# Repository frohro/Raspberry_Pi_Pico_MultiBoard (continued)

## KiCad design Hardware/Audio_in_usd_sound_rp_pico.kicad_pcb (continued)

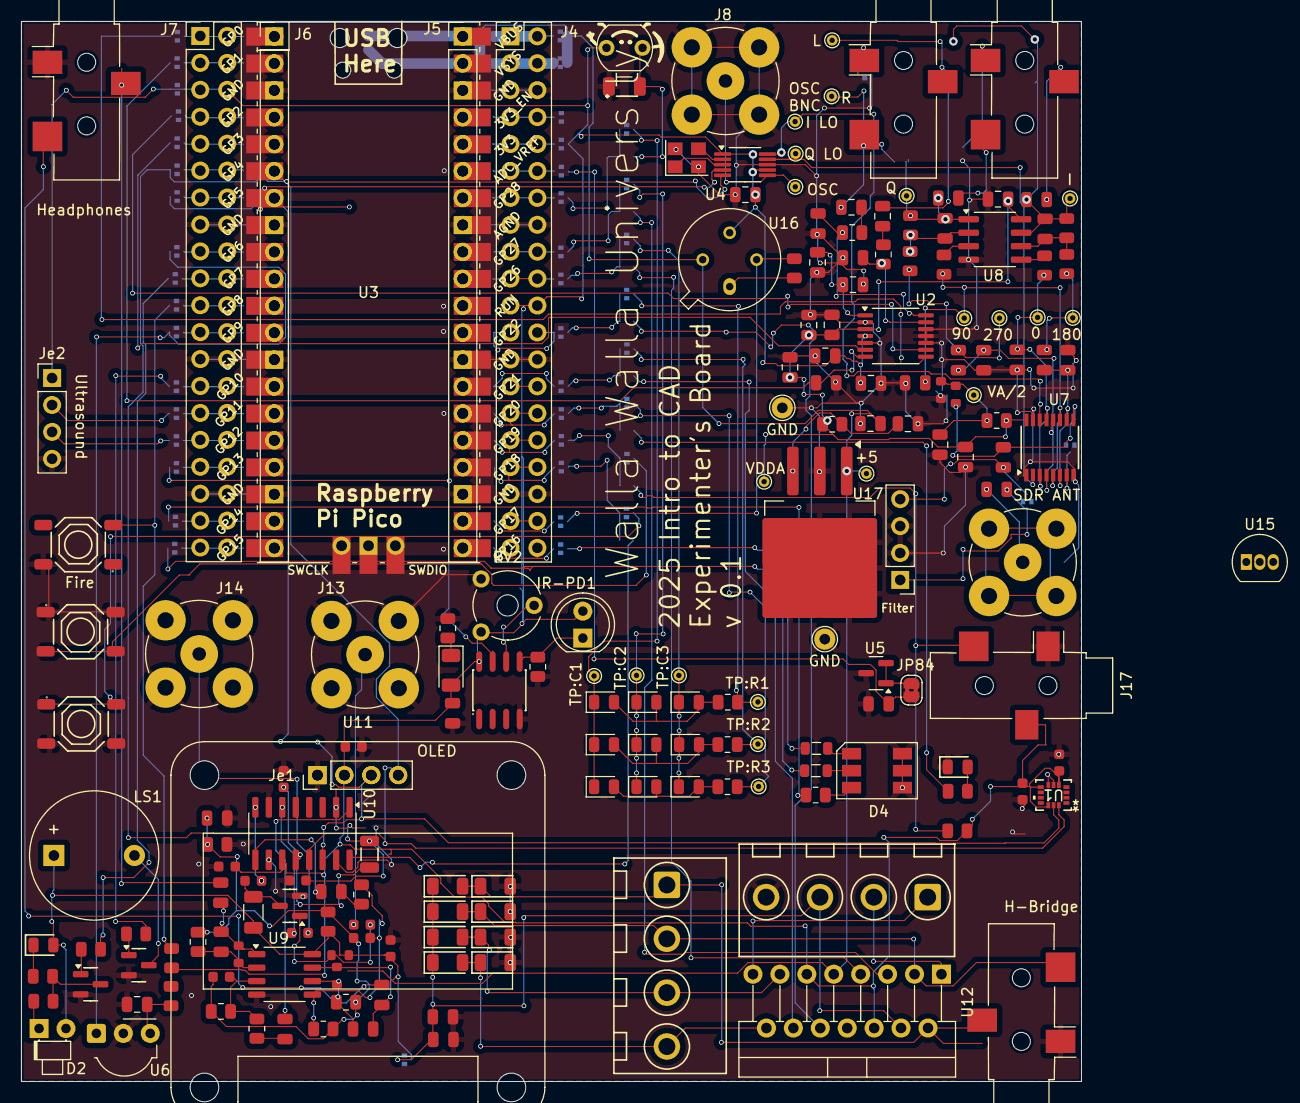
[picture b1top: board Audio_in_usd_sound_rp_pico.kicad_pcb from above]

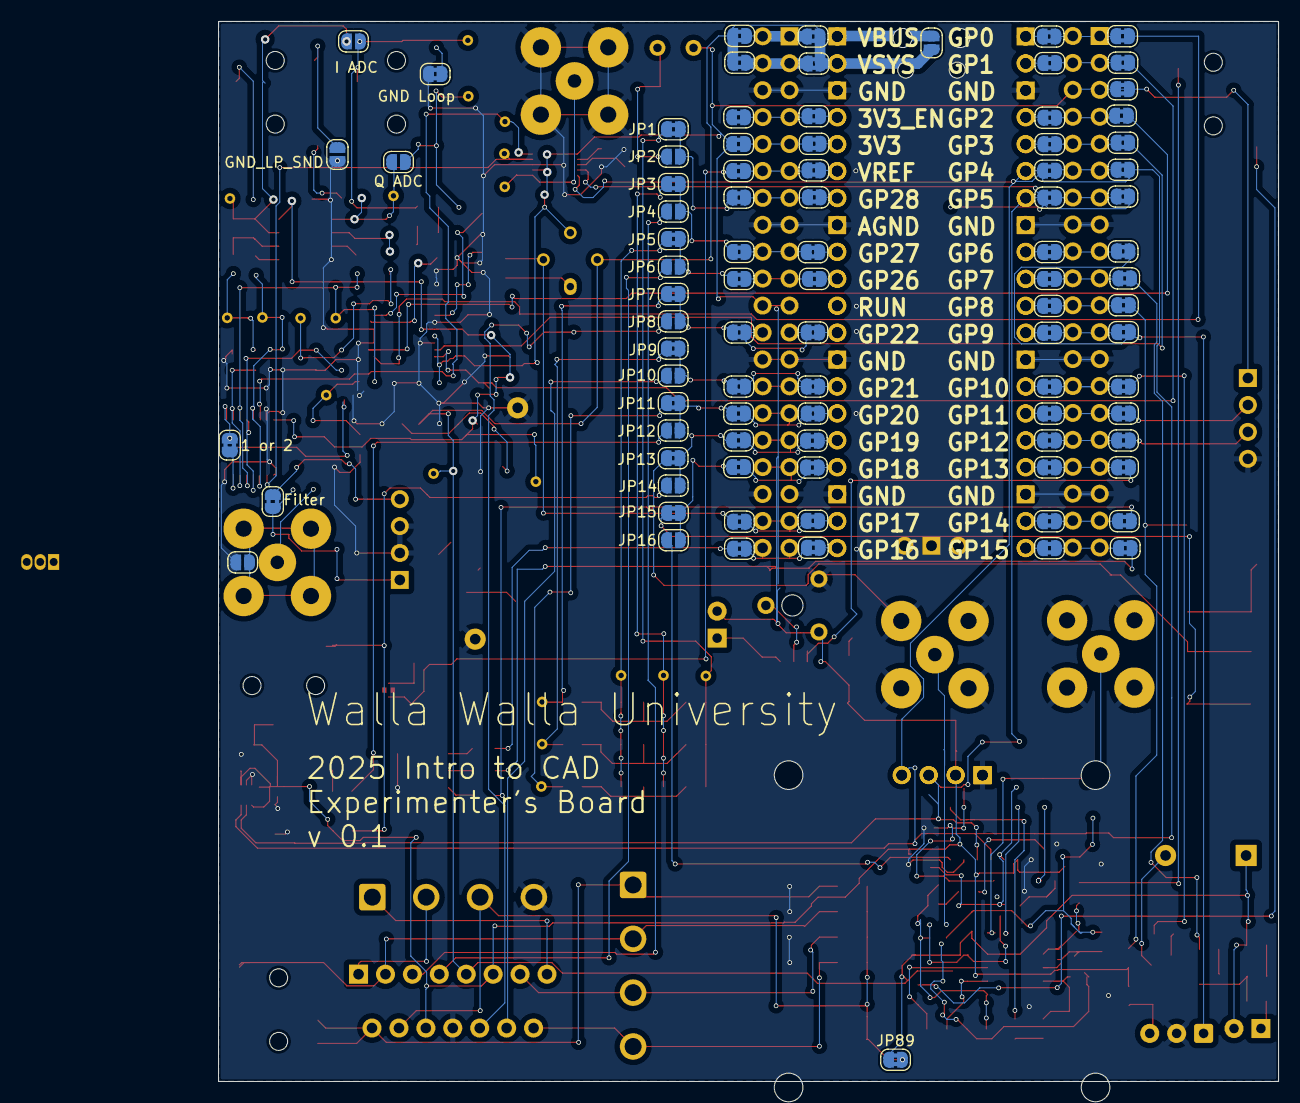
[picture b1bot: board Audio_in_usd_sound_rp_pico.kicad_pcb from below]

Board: 2 copper layers, 100.0 x 100.0 mm, 275 parts (88 on the bottom side), 189 nets.

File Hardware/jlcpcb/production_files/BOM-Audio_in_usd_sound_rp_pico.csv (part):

Comment,Designator,Footprint,LCSC,Quantity
PhotoResistor,R37,R_LDR_5.1x4.3mm_P3.4mm_Vertical,C10077,1
220pF,"C14,C33,C42",C_0805,C107145,3
TSOP4438,U6,Vishay_MOLD-3Pin,C124647,1
100nF,"C2,C38,C41,C47,C48,C52",C_0603,C14663,6
MS5351M,U4,MSOP-10_3x3mm_P0.5mm,C1509083,1
10uF,"C12,C31,C32,C39,C40,C44,C45,C56,C57,C8,C9",C_0805_2012Metric,C15850,11
2.2nF,"C35,C54",C_0603,C1604,2
22pF,"C36,C37",C_0603,C1653,2
100Ω,"R31,R4,R43",R_0805,C17408,3
10k,"R12,R42,R6",R_0805_2012Metric,C17414,3
10Ω,"R13,R14,R15,R16",R_0805,C17415,4
4.7nF,"C16,C21,C22,C24,C27,C6,C7",C_0805,C1744,7
15k,R25,R_0805_2012Metric,C17475,1
1kΩ,"R7,R8",R_0805,C17513,2
200,"R2,R3",R_0805_2012Metric,C17544,2
2kΩ,"R17,R18,R29,R30",R_0805,C17604,4
3.9k,"R23,R28",R_0805_2012Metric,C17614,2
33Ω,R9,R_0805,C17634,1
680,"R39,R40,R41",R_0805_2012Metric,C17798,3
68Ω,R5,R_0805,C17802,1
8.2k,"R21,R27",R_0805_2012Metric,C17828,2
100pF,"C28,C29",C_0805,C1790,2
1kΩ,R38,R_1206_3216Metric,C17902,1
1N4004W,"D10,D11,D12,D5,D6,D7,D8,D9",D_SOD-123FL,C18199087,8
IR LED IR908-7C-F,D2,LED_D1.8mm_W1.8mm_H2.4mm_Horizontal_O1.27mm_Z8.2mm,C183794,1
ADC IN,"J1,J12,J15,J16,J17",Jack_3.5mm_CUI_SJ-3523-SMT_Horizontal,C18594,5
L298N,U12,TO-220-15_P2.54x2.54mm_StaggerOdd_Lead4.58mm_Vertical,C19922,1
1kΩ,R11,R_0603,C21190,1
Si4732,U10,SOIC-16_3.9x9.9mm_P1.27mm,C2155558,1
DS18B20A10T6,U15,TO-92_Inline,C22360667,1
Green,"D1,D3",D_0805,C2297,2
39kΩ,"R10,R20",R_0603,C23153,2
1,R44,R_0805_2012Metric,C25271,1
B 100Ω,"R32,R33",L_0805_2012Metric,C25277,2
100kΩ,R22,R_0603,C25803,1
10kΩ,R1,R_0603,C25804,1
Conn_01x04_Socket,"Je1,Je2,Je3",PinHeader_1x04_P2.54mm_Vertical_Female,C2718488,3
1uF,"C18,C19,C25,C26,C3,C4,C46",C_0805,C28323,7
LM2937xS,U17,TO-263-3_TabPin2,C2902486,1
Conn_01x20,"J5,J6",PinHeader_1x20_P2.54mm_Vertical,C2905423,2
Conn_02x20_Counter_Clockwise,"J4,J7",PinSocket_2x20_P2.54mm_Vertical_Counterclockwise,C2977589,2
"Screw Terminal, 4Px5.08mm, 20A","T1,T2",CONN-TH_4P-P5.08_DB129VG-5.08-4P-GN-S,C2981774,2
PI5C3253CQEX,U7,SSOP-16_3.9x4.9mm_P0.635mm,C3001703,1
CJ431,U5,SOT-23,C3113,1
"Tactile Button, 160gf","S2,SW1,SW2",SW-SMD_4P-L5.1-W5.1-P3.70-LS6.5-TL-2,C318884,3
Q13FC1350000400,X1,FC-135R_L3.2-W1.5,C32346,1
Speaker,LS1,Buzzer_12x9.5RM7.6,C409842,1
1k,R24,R_1206_3216Metric,C4410,1
0.1uF,"C10,C11,C13,C15,C20,C23,C30,C49,C50,C51,C55",C_0805_2012Metric,C49678,11
~,U16,TO-33-4_Window-Taylan,C5380082,1
PCM1808PWR,U2,TSSOP-14_4.4x5mm_P0.65mm,C55513,1
10nF,"C34,C43",C_0603,C57112,2
MMBT2222A,Q3,Q_SOT-23,C7420351,1
LM393DR2G,U13,SOIC-8_L5.0-W4.0-P1.27-LS6.0-BL,C7955,1
LED,"D13,D14,D15,D16,D17,D18,D19,D20,D21",LED_0805_2012Metric,C84256,9
MMBT2222A 1P,"Q1,Q2",Q_SOT-23,C8512,2
X322525MSB4SI,Y1,Crystal_SMD_3225-4Pin_3.2x2.5mm,C9006,1
OPA1612AxD,U8,SOIC-8_3.9x4.9mm_P1.27mm,C94590,1
LSM6DSO32TR,U1,LGA-14L_2P5X3X0P83_STM,,1
LM358,U9,SOP-8_3.9x4.9mm_P1.27mm,,1
ANT_BNC,J14,BNC_TEConnectivity_1478204_Vertical,,1
I LO,TP3,TestPoint_THTPad_D1.0mm_Drill0.5mm,,1
Q LO,TP4,TestPoint_THTPad_D1.0mm_Drill0.5mm,,1
10K,R35,R_0805_2012Metric,,1
+5,TP25,TestPoint_THTPad_D1.0mm_Drill0.5mm,,1
VA/2,TP11,TestPoint_THTPad_D1.0mm_Drill0.5mm,,1
15k,R19,R_0805_2012Metric,,1
90,TP16,TestPoint_THTPad_D1.0mm_Drill0.5mm,,1
0.1uF,C17,C_0805_2012Metric,,1
R 300Ω,R34,R_0805_2012Metric,,1
0,TP14,TestPoint_THTPad_D1.0mm_Drill0.5mm,,1
GND,TP10,TestPoint_THTPad_D2.0mm_Drill1.0mm,,1
OSC,TP5,TestPoint_THTPad_D1.0mm_Drill0.5mm,,1
GND,TP12,TestPoint_THTPad_D2.0mm_Drill1.0mm,,1
L,TP1,TestPoint_THTPad_D1.0mm_Drill0.5mm,,1
Jumper_2_Bridged,JP84,SolderJumper-2_P1.3mm_Bridged2Bar_RoundedPad1.0x1.5mm,,1
270,TP15,TestPoint_THTPad_D1.0mm_Drill0.5mm,,1
BNC,J8,BNC_TEConnectivity_1478204_Vertical,,1
270R,R36,R_0805_2012Metric,,1
SDR ANT,J11,BNC_TEConnectivity_1478204_Vertical,,1
Q,TP18,TestPoint_THTPad_D1.0mm_Drill0.5mm,,1
180,TP13,TestPoint_THTPad_D1.0mm_Drill0.5mm,,1
C784540,D4,LED footprint,,1
VDDA,TP26,TestPoint_THTPad_D1.0mm_Drill0.5mm,,1
R,TP2,TestPoint_THTPad_D1.0mm_Drill0.5mm,,1
R_Potentiometer_US,RV2,Potentiometer_Piher_PT-6-V_Vertical_Hole,,1
I,TP17,TestPoint_THTPad_D1.0mm_Drill0.5mm,,1
ANT_BNC,J13,BNC_TEConnectivity_1478204_Vertical,,1
Jumper_2_Open,JP12,SolderJumper-2_P1.3mm_Open_RoundedPad1.0x1.5mm,,1
Jumper_2_Bridged,JP28,SolderJumper-2_P1.3mm_Bridged2Bar_RoundedPad1.0x1.5mm,,1
Jumper_2_Bridged,JP41,SolderJumper-2_P1.3mm_Bridged2Bar_RoundedPad1.0x1.5mm,,1
Jumper_2_Bridged,JP66,SolderJumper-2_P1.3mm_Bridged2Bar_RoundedPad1.0x1.5mm,,1
Jumper_2_Bridged,JP83,SolderJumper-2_P1.3mm_Bridged2Bar_RoundedPad1.0x1.5mm,,1
Jumper_2_Open,JP8,SolderJumper-2_P1.3mm_Open_RoundedPad1.0x1.5mm,,1
Jumper_2_Bridged,JP81,SolderJumper-2_P1.3mm_Bridged2Bar_RoundedPad1.0x1.5mm,,1
Jumper_2_Bridged,JP79,SolderJumper-2_P1.3mm_Bridged2Bar_RoundedPad1.0x1.5mm,,1
Groundloop RX_NS,JP85,SolderJumper-2_P1.3mm_Open_RoundedPad1.0x1.5mm,,1
Jumper_2_Bridged,JP31,SolderJumper-2_P1.3mm_Bridged2Bar_RoundedPad1.0x1.5mm,,1
Jumper_2_Bridged,JP74,SolderJumper-2_P1.3mm_Bridged2Bar_RoundedPad1.0x1.5mm,,1
Jumper_2_Bridged,JP78,SolderJumper-2_P1.3mm_Bridged2Bar_RoundedPad1.0x1.5mm,,1
Jumper_2_Bridged,JP13,SolderJumper-2_P1.3mm_Bridged2Bar_RoundedPad1.0x1.5mm,,1
Jumper_2_Bridged,JP22,SolderJumper-2_P1.3mm_Bridged2Bar_RoundedPad1.0x1.5mm,,1
Jumper_2_Bridged,JP69,SolderJumper-2_P1.3mm_Bridged2Bar_RoundedPad1.0x1.5mm,,1
Jumper_2_Bridged,JP87,SolderJumper-2_P1.3mm_Bridged2Bar_RoundedPad1.0x1.5mm,,1
Jumper_2_Bridged,JP44,SolderJumper-2_P1.3mm_Bridged2Bar_RoundedPad1.0x1.5mm,,1
Jumper_2_Bridged,JP47,SolderJumper-2_P1.3mm_Bridged2Bar_RoundedPad1.0x1.5mm,,1
GND_LP_SND,JP18,SolderJumper-2_P1.3mm_Open_RoundedPad1.0x1.5mm,,1
Jumper_2_Bridged,JP73,SolderJumper-2_P1.3mm_Bridged2Bar_RoundedPad1.0x1.5mm,,1
Jumper_2_Bridged,JP59,SolderJumper-2_P1.3mm_Bridged2Bar_RoundedPad1.0x1.5mm,,1
Jumper_2_Bridged,JP40,SolderJumper-2_P1.3mm_Bridged2Bar_RoundedPad1.0x1.5mm,,1
GND_LP_SND,JP19,SolderJumper-2_P1.3mm_Open_RoundedPad1.0x1.5mm,,1
Jumper_2_Bridged,JP42,SolderJumper-2_P1.3mm_Bridged2Bar_RoundedPad1.0x1.5mm,,1
Jumper_2_Bridged,JP15,SolderJumper-2_P1.3mm_Bridged2Bar_RoundedPad1.0x1.5mm,,1
Jumper_2_Bridged,JP60,SolderJumper-2_P1.3mm_Bridged2Bar_RoundedPad1.0x1.5mm,,1
Jumper_2_Bridged,JP34,SolderJumper-2_P1.3mm_Bridged2Bar_RoundedPad1.0x1.5mm,,1
Jumper_2_Bridged,JP80,SolderJumper-2_P1.3mm_Bridged2Bar_RoundedPad1.0x1.5mm,,1
Jumper_2_Bridged,JP67,SolderJumper-2_P1.3mm_Bridged2Bar_RoundedPad1.0x1.5mm,,1
Jumper_2_Bridged,JP82,SolderJumper-2_P1.3mm_Bridged2Bar_RoundedPad1.0x1.5mm,,1
Jumper_2_Bridged,JP11,SolderJumper-2_P1.3mm_Bridged2Bar_RoundedPad1.0x1.5mm,,1
Jumper_2_Bridged,JP23,SolderJumper-2_P1.3mm_Bridged2Bar_RoundedPad1.0x1.5mm,,1
Jumper_2_Bridged,JP77,SolderJumper-2_P1.3mm_Bridged2Bar_RoundedPad1.0x1.5mm,,1
Jumper_2_Bridged,JP1,SolderJumper-2_P1.3mm_Bridged2Bar_RoundedPad1.0x1.5mm,,1
Jumper_2_Bridged,JP27,SolderJumper-2_P1.3mm_Bridged2Bar_RoundedPad1.0x1.5mm,,1
Jumper_2_Bridged,JP39,SolderJumper-2_P1.3mm_Bridged2Bar_RoundedPad1.0x1.5mm,,1
Jumper_2_Bridged,JP3,SolderJumper-2_P1.3mm_Bridged2Bar_RoundedPad1.0x1.5mm,,1
Jumper_2_Bridged,JP17,SolderJumper-2_P1.3mm_Bridged2Bar_RoundedPad1.0x1.5mm,,1
Jumper_2_Bridged,JP5,SolderJumper-2_P1.3mm_Bridged2Bar_RoundedPad1.0x1.5mm,,1
Jumper_2_Bridged,JP63,SolderJumper-2_P1.3mm_Bridged2Bar_RoundedPad1.0x1.5mm,,1
Jumper_2_Bridged,JP86,SolderJumper-2_P1.3mm_Bridged2Bar_RoundedPad1.0x1.5mm,,1
Jumper_2_Bridged,JP51,SolderJumper-2_P1.3mm_Bridged2Bar_RoundedPad1.0x1.5mm,,1
Jumper_2_Bridged,JP68,SolderJumper-2_P1.3mm_Bridged2Bar_RoundedPad1.0x1.5mm,,1
Jumper_2_Bridged,JP38,SolderJumper-2_P1.3mm_Bridged2Bar_RoundedPad1.0x1.5mm,,1
Jumper_2_Bridged,JP75,SolderJumper-2_P1.3mm_Bridged2Bar_RoundedPad1.0x1.5mm,,1
Jumper_2_Bridged,JP65,SolderJumper-2_P1.3mm_Bridged2Bar_RoundedPad1.0x1.5mm,,1
Jumper_2_Bridged,JP32,SolderJumper-2_P1.3mm_Bridged2Bar_RoundedPad1.0x1.5mm,,1
Jumper_2_Bridged,JP29,SolderJumper-2_P1.3mm_Bridged2Bar_RoundedPad1.0x1.5mm,,1
Jumper_2_Bridged,JP49,SolderJumper-2_P1.3mm_Bridged2Bar_RoundedPad1.0x1.5mm,,1
Jumper_2_Bridged,JP45,SolderJumper-2_P1.3mm_Bridged2Bar_RoundedPad1.0x1.5mm,,1
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
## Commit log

2025-04-10 Initial commit with complete project structure.!
2025-04-10 Changed to SoftI2C, because hardware I2C doesn't seem to work
2025-04-29 Hardware errors found.
2025-04-29 Finding bugs in Si4732, etc.
2025-05-23 Update README with details about Pico clone power supply differences and remove obsolete KiCad lock file
2025-05-23 Add details about Pico power supply schematic and Si5351a test observations in README
2025-05-23 Update README to clarify Si5351a test results with additional board information
2025-05-23 Add details about Si5351a tests and SDR receiver performance to README
